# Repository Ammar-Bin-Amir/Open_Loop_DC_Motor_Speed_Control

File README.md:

# Open Loop DC Motor Speed Control

The function of speed control in DC motors is very essential in the achievement of desirable outputs. In this project, the speed of dc motor is controlled manually using potentiometer along with the assistance of human. The purpose of this project is to implement the concepts of linear control system and to find out the open loop system's functionality.

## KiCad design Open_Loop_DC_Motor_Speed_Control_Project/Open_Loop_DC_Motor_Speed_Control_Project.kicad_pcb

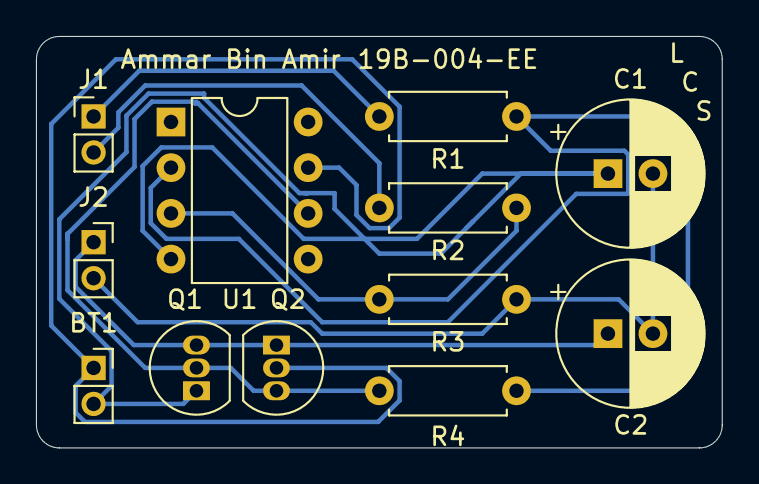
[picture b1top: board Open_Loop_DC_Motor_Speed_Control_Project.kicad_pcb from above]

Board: 2 copper layers, 38.1 x 22.9 mm, 12 parts (0 on the bottom side), 9 nets.

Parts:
BT1: 9V; PinSocket_1x02_P2.00mm_Vertical
C1, C2: 470μF,16V; CP_Radial_D8.0mm_P2.50mm
J1: Conn_01x02_Male; PinHeader_1x02_P2.00mm_Vertical
J2: Conn_01x02_Female; PinSocket_1x02_P2.00mm_Vertical
Q1: BC546; TO-92_Inline
Q2: BC636; TO-92_Inline
R1, R2, R3, R4: 10kΩ; R_Axial_DIN0207_L6.3mm_D2.5mm_P7.62mm_Horizontal
U1: LM741; DIP-8_W7.62mm

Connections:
GND: C1.2, C2.2, J2.2, R3.1
unnamed: BT1.1, Q2.2, U1.7
unnamed: BT1.2, C1.1, Q1.1, U1.4
unnamed: C2.1, J2.1, Q1.3, Q2.1
unnamed: J1.1, R1.2
unnamed: J1.2, R2.2
unnamed: Q1.2, Q2.3, R4.1, U1.6
unnamed: R1.1, R4.2, U1.2
unnamed: R2.1, R3.2, U1.3
